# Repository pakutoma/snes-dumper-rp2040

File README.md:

# snes-dumper-rp2040
##  概要
RP2040マイコンを使ったスーパーファミコンのROM吸い出し機の実験的実装です。
MicroPythonで書かれており、PIOやDMAによって吸い出しの高速化を図っています。
吸い出し速度は200KB/sほどです。

## ハードウェアのパーツ
- メイン基板（/board のKiCadプロジェクト）
  - PCBプロトタイプ業者（JLCPCB等）に発注してください
- RP2040マイコンボードキット（秋月電子通商）
- 74HC273 * 3
- 2.5mmピッチ62ピンソケット（SNES用）
  - Aliexpressとかで買うといいです

## 使い方
1. ボードにclientの中身を書き込む
2. host.pyを実行する
3. 数分で吸い出される（失敗なら端子を掃除すると良い）

## 対応ROM
- LoROM
- HiROM
- ExHiROM

## 非対応ROM
- SA-1
- その他、動かないもの

## 参考にしたもの
- [SNES Development Wiki](https://snes.nesdev.org/wiki/Main_Page)
  - [Cartridge connector](https://snes.nesdev.org/wiki/Cartridge_connector)
  - [Memory map](https://snes.nesdev.org/wiki/Memory_map)
  - [ROM header](https://snes.nesdev.org/wiki/ROM_header)

## ライセンス
Apache License 2.0

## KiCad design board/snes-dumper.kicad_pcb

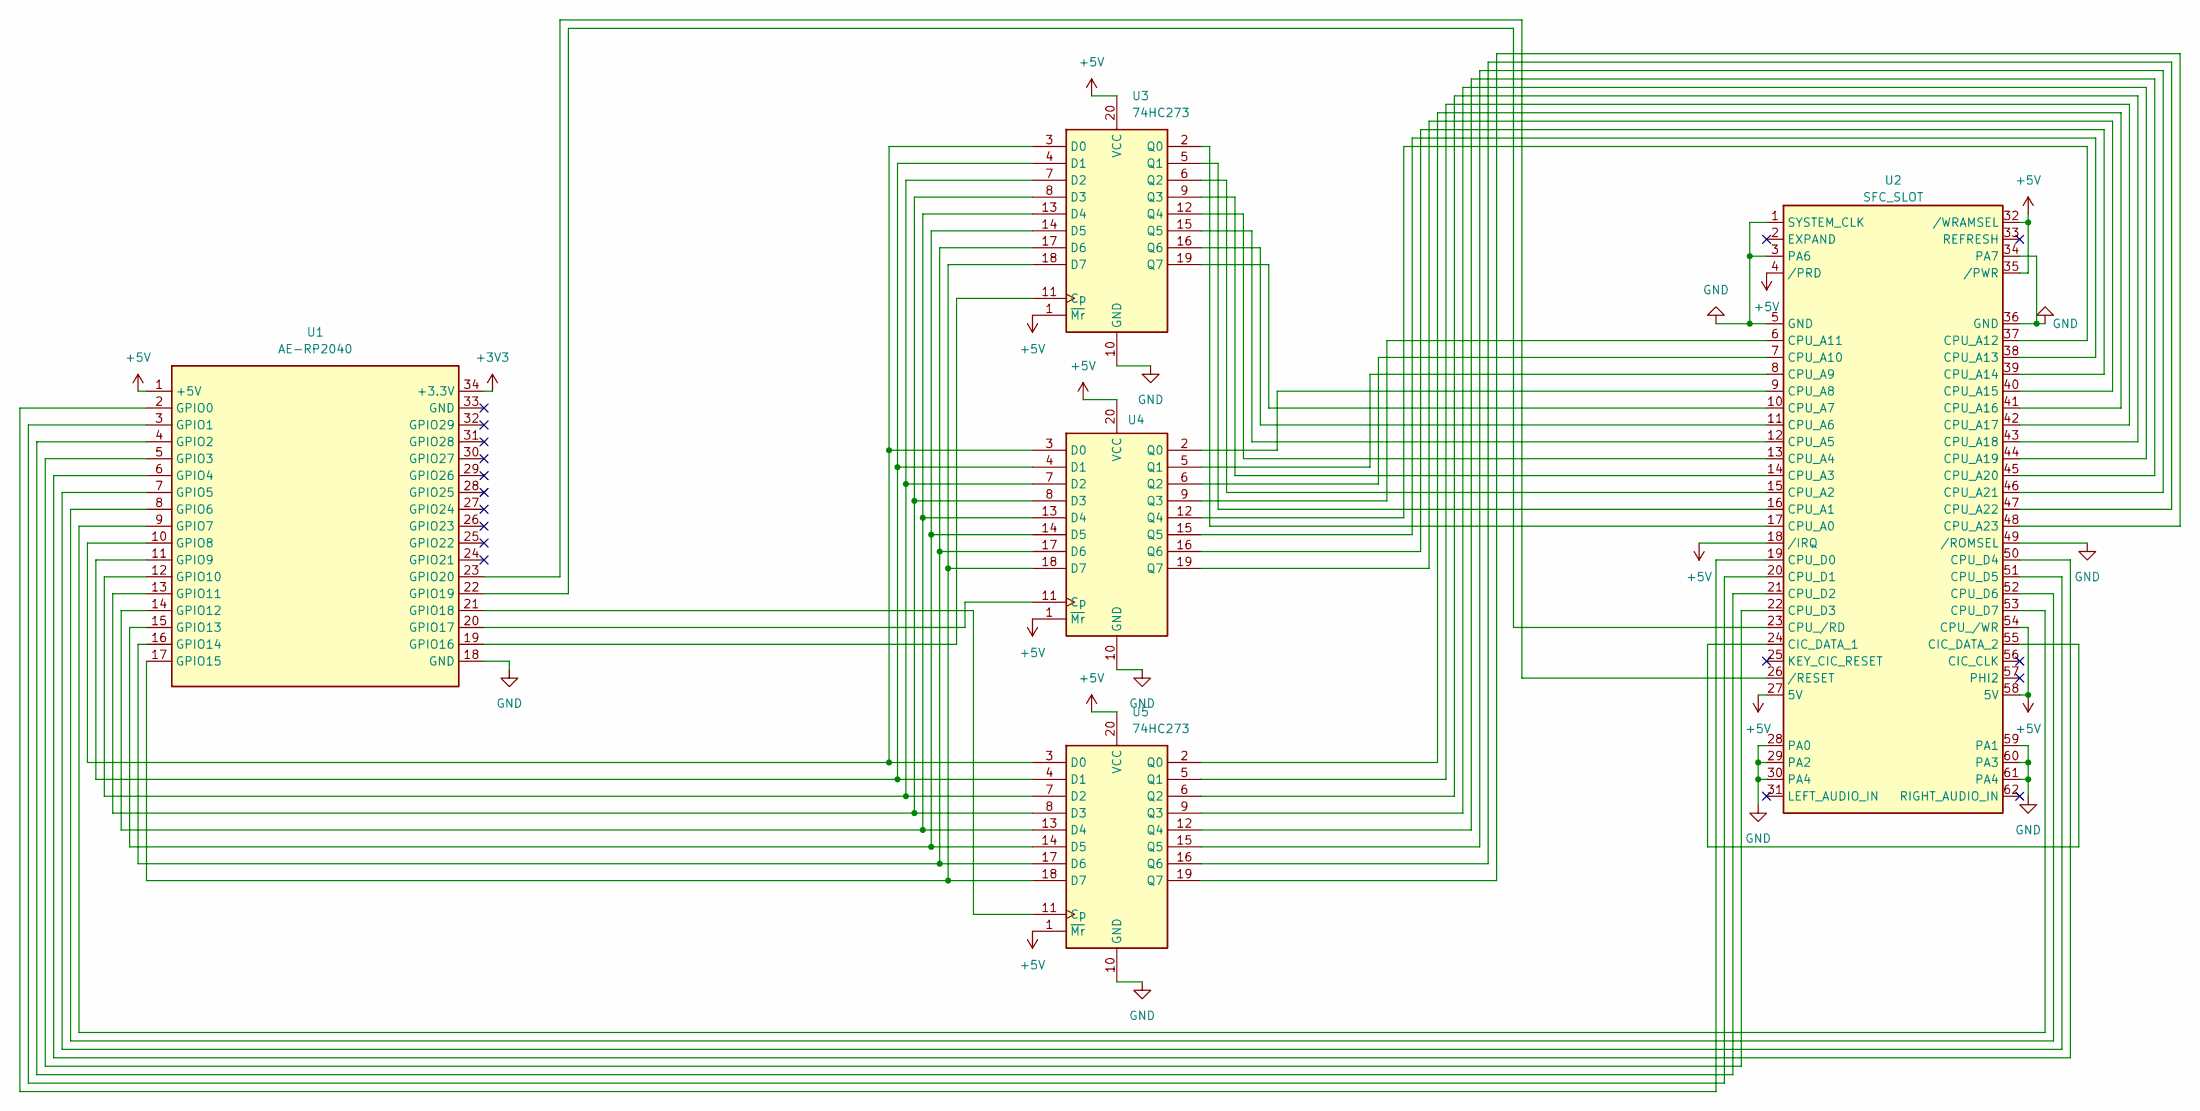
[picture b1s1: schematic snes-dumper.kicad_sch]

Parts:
U1: AE-RP2040
U2: SFC_SLOT; SFC_CART
U3, U4, U5: 74HC273; DIP-20_W7.62mm_Socket

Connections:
+3V3: U1.34 (+3.3V)
+5V: U1.1 (+5V), U2.4 (/PRD), U2.18 (/IRQ), U2.27 (5V), U2.32 (/WRAMSEL), U2.35 (/PWR), U2.54 (CPU_/WR), U2.58 (5V), U3.1 (~Mr), U3.20 (VCC), U4.1 (~Mr), U4.20 (VCC), U5.1 (~Mr), U5.20 (VCC)
GND: U1.18 (GND), U2.1 (SYSTEM_CLK), U2.3 (PA6), U2.5 (GND), U2.28 (PA0), U2.29 (PA2), U2.30 (PA4), U2.34 (PA7), U2.36 (GND), U2.49 (/ROMSEL), U2.59 (PA1), U2.60 (PA3), U2.61 (PA4), U3.10 (GND), U4.10 (GND), U5.10 (GND)
unnamed: U1.2 (GPIO0), U2.19 (CPU_D0)
unnamed: U1.3 (GPIO1), U2.20 (CPU_D1)
unnamed: U1.4 (GPIO2), U2.21 (CPU_D2)
unnamed: U1.5 (GPIO3), U2.22 (CPU_D3)
unnamed: U1.6 (GPIO4), U2.50 (CPU_D4)
unnamed: U1.7 (GPIO5), U2.51 (CPU_D5)
unnamed: U1.8 (GPIO6), U2.52 (CPU_D6)
unnamed: U1.9 (GPIO7), U2.53 (CPU_D7)
unnamed: U1.10 (GPIO8), U3.3 (D0), U4.3 (D0), U5.3 (D0)
unnamed: U1.11 (GPIO9), U3.4 (D1), U4.4 (D1), U5.4 (D1)
unnamed: U1.12 (GPIO10), U3.7 (D2), U4.7 (D2), U5.7 (D2)
unnamed: U1.13 (GPIO11), U3.8 (D3), U4.8 (D3), U5.8 (D3)
unnamed: U1.14 (GPIO12), U3.13 (D4), U4.13 (D4), U5.13 (D4)
unnamed: U1.15 (GPIO13), U3.14 (D5), U4.14 (D5), U5.14 (D5)
unnamed: U1.16 (GPIO14), U3.17 (D6), U4.17 (D6), U5.17 (D6)
unnamed: U1.17 (GPIO15), U3.18 (D7), U4.18 (D7), U5.18 (D7)
unnamed: U1.19 (GPIO16), U3.11 (Cp)
unnamed: U1.20 (GPIO17), U4.11 (Cp)
unnamed: U1.21 (GPIO18), U5.11 (Cp)
unnamed: U1.22 (GPIO19), U2.23 (CPU_/RD)
unnamed: U1.23 (GPIO20), U2.26 (/RESET)
unnamed: U2.24 (CIC_DATA_1), U2.55 (CIC_DATA_2)
unnamed: U2.17 (CPU_A0), U3.2 (Q0)
unnamed: U2.16 (CPU_A1), U3.5 (Q1)
unnamed: U2.15 (CPU_A2), U3.6 (Q2)
unnamed: U2.14 (CPU_A3), U3.9 (Q3)
unnamed: U2.13 (CPU_A4), U3.12 (Q4)
unnamed: U2.12 (CPU_A5), U3.15 (Q5)
unnamed: U2.11 (CPU_A6), U3.16 (Q6)
unnamed: U2.10 (CPU_A7), U3.19 (Q7)
unnamed: U2.9 (CPU_A8), U4.2 (Q0)
unnamed: U2.8 (CPU_A9), U4.5 (Q1)
unnamed: U2.7 (CPU_A10), U4.6 (Q2)
unnamed: U2.6 (CPU_A11), U4.9 (Q3)
unnamed: U2.37 (CPU_A12), U4.12 (Q4)
unnamed: U2.38 (CPU_A13), U4.15 (Q5)
unnamed: U2.39 (CPU_A14), U4.16 (Q6)
unnamed: U2.40 (CPU_A15), U4.19 (Q7)
unnamed: U2.41 (CPU_A16), U5.2 (Q0)
unnamed: U2.42 (CPU_A17), U5.5 (Q1)
unnamed: U2.43 (CPU_A18), U5.6 (Q2)
unnamed: U2.44 (CPU_A19), U5.9 (Q3)
unnamed: U2.45 (CPU_A20), U5.12 (Q4)
unnamed: U2.46 (CPU_A21), U5.15 (Q5)
unnamed: U2.47 (CPU_A22), U5.16 (Q6)
unnamed: U2.48 (CPU_A23), U5.19 (Q7)

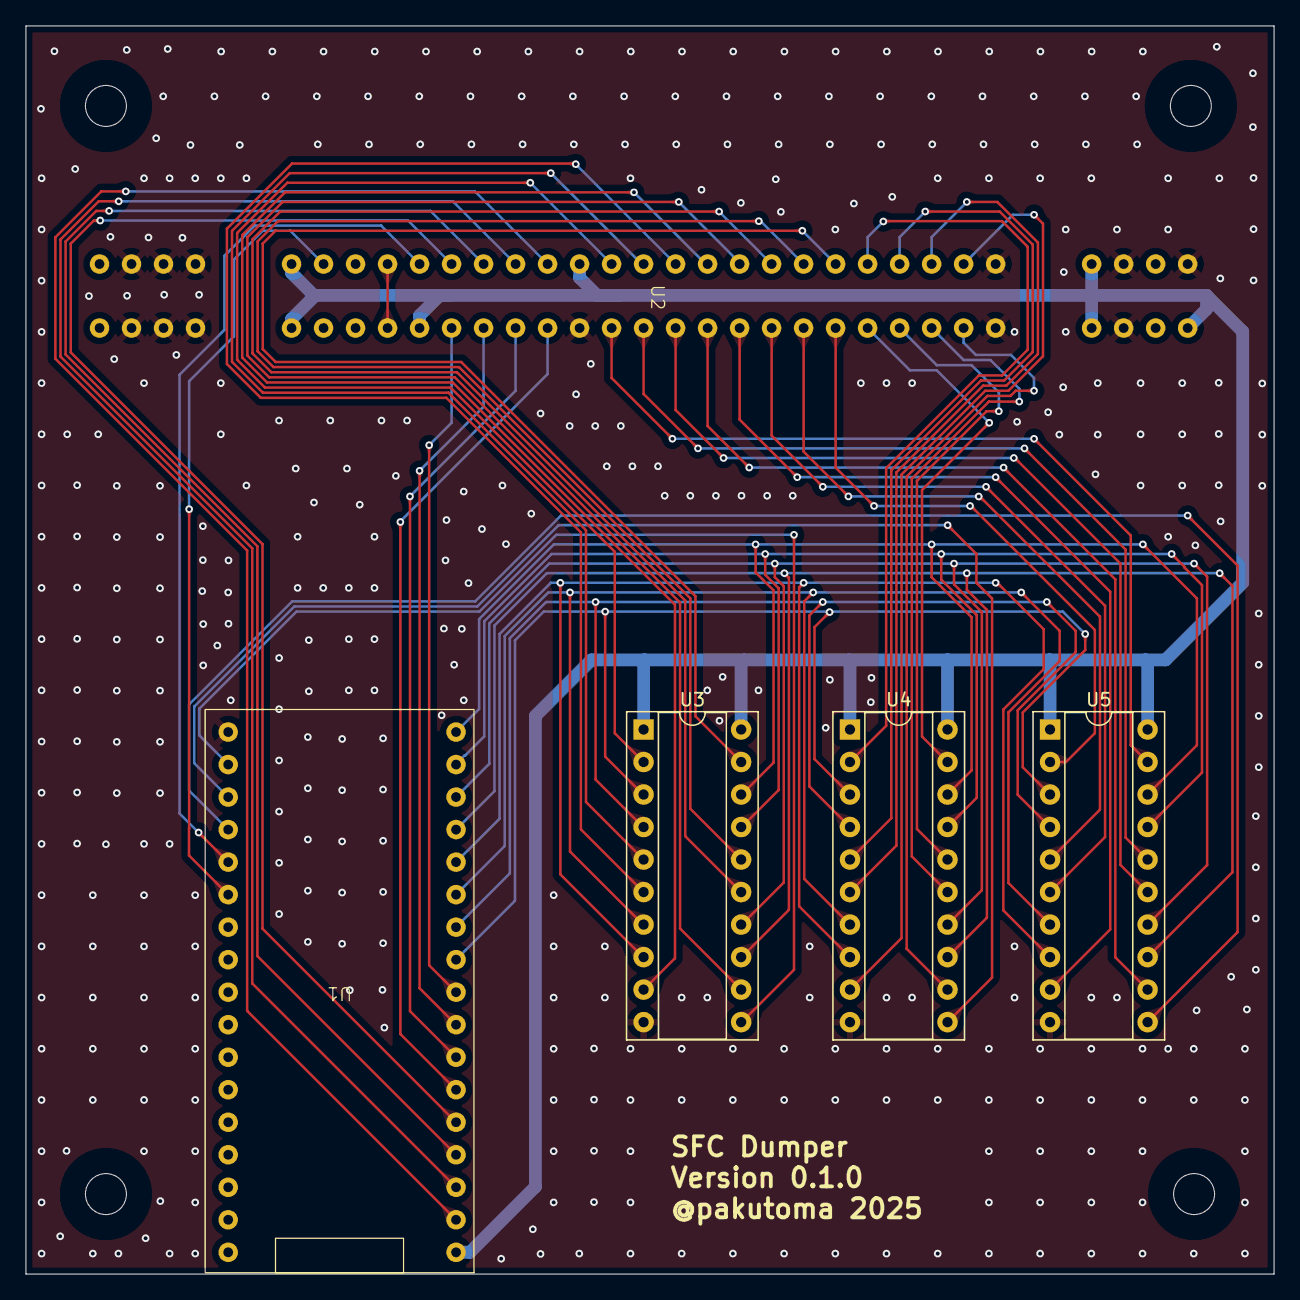
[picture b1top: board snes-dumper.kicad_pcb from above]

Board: 2 copper layers, 97.5 x 97.5 mm, 5 parts (0 on the bottom side), 48 nets.

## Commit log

2025-04-16 add board
2025-04-18 support new board
2025-04-20 support new board with PIO
2025-05-10 support exhirom
